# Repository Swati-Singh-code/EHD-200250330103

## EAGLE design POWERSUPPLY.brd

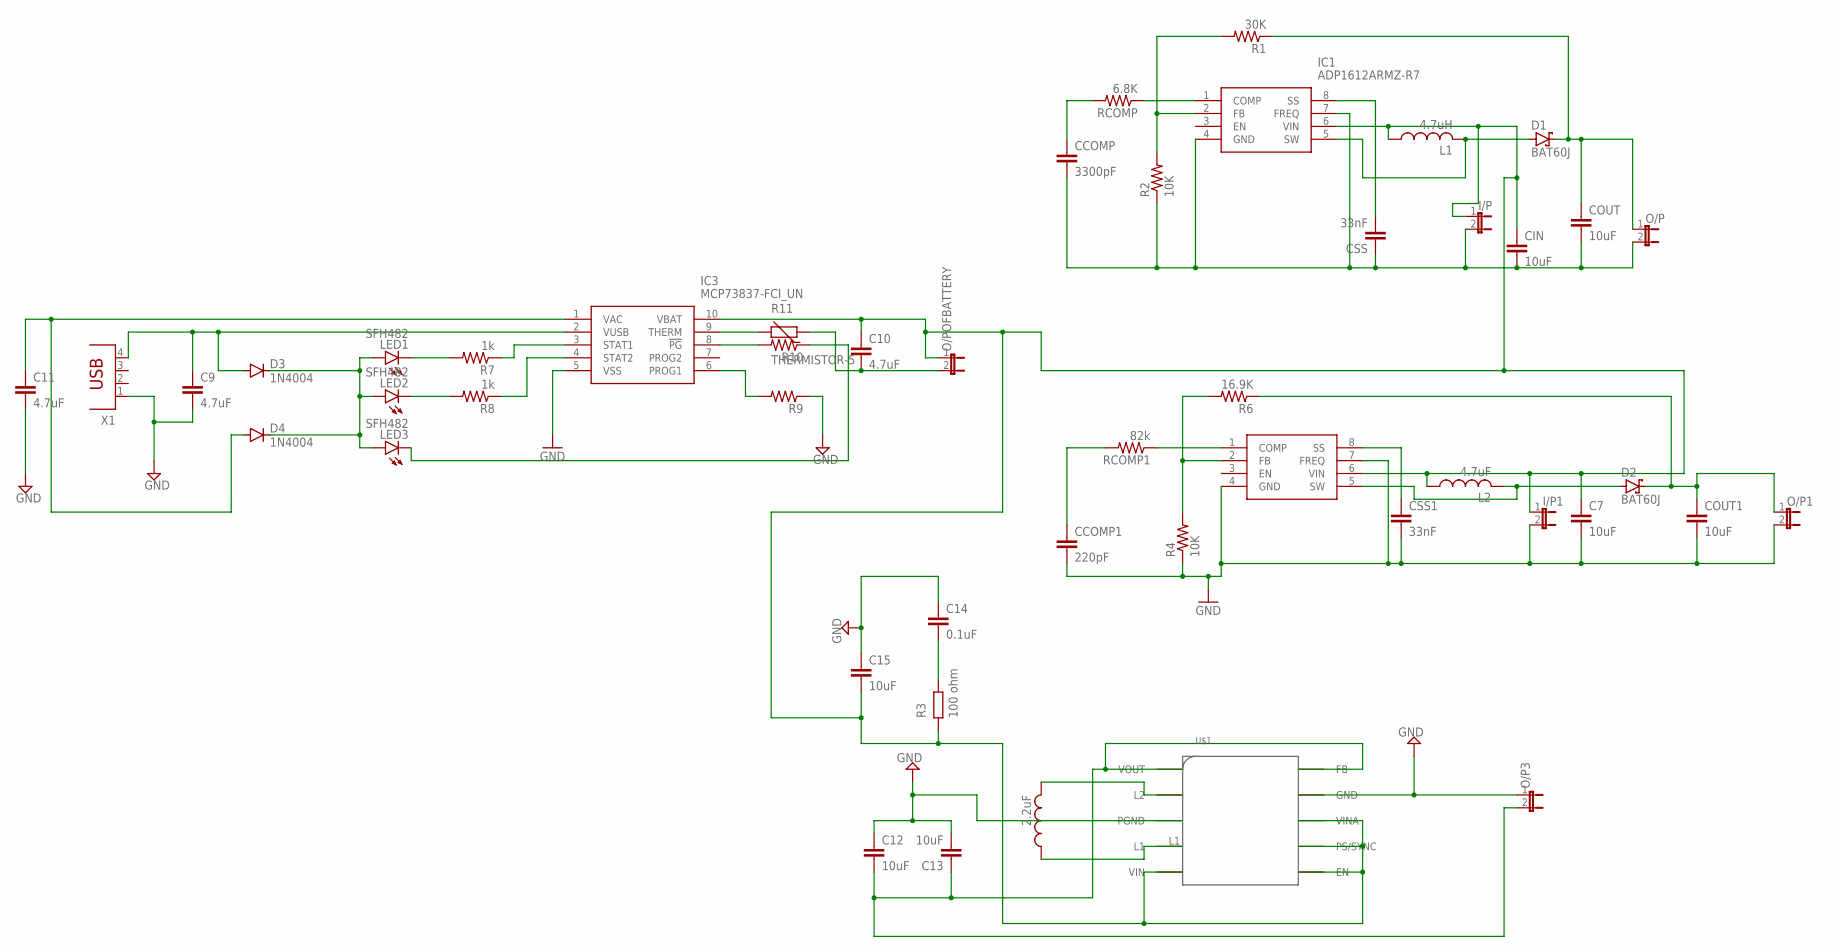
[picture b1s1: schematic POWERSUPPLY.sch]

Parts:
C7, C12, C13, C15: 10uF; C2.5-3
C9, C10, C11: 4.7uF; C2.5-3
C14: 0.1uF; C2.5-3
CCOMP: 3300pF; C2.5-3
CCOMP1: 220pF; C2.5-3
CIN: 10uF; C2.5-3
COUT, COUT1: 10uF; C2.5-3
CSS, CSS1: 33nF; C2.5-3
D1, D2: BAT60J; SOD323_ST
D3, D4: 1N4004; DO41-10
I/P, I/P1: JP1E; JP1
IC1: ADP1612ARMZ-R7; SOP65P490X110-8N
IC2: ADP1613ARMZ-R7; SOP65P490X110-8N
IC3: MCP73837-FCI_UN; SOP50P490X110-10N
L1: 4.7uH; 0207/5V
L2: 4.7uF; 0207/5V
L3: 2.2uF; 0207/5V
LED1, LED2, LED3: SFH482
O/P, O/P3: JP1E; JP1
O/P1: 3.3V; JP1
O/POFBATTERY: JP1E; JP1
R1: 30K; 0204/7
R2, R4: 10K; 0204/7
R6: 16.9K; 0204/7
R7, R8: 1k; 0204/7
R9, R10: R-US_0204/7; 0204/7
R11: THERMISTOR-5; R-5
RCOMP: 6.8K; 0204/7
RCOMP1: 82k; 0204/7
U$1: TPS63002
X1: PN87520

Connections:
GND: C7.2, C9.2, C11.2, C12.1, C13.2, C14.1, C15.1, CCOMP1.2, COUT1.2, CSS1.2, I/P1.2, IC2.4 (GND), IC2.7 (FREQ), IC3.5 (VSS), O/P1.2, O/P3.1, R4.1, R9.1, U$1.GND, U$1.PGND, X1.1
unnamed: CCOMP.1, RCOMP.2
unnamed: IC1.1 (COMP), RCOMP.1
unnamed: CCOMP.2, CIN.2, COUT.2, CSS.1, I/P.2, IC1.4 (GND), IC1.7 (FREQ), O/P.2, R2.1
unnamed: IC1.2 (FB), R1.2, R2.2
unnamed: CSS.2, IC1.8 (SS)
unnamed: IC3.4 (STAT2), R8.1
unnamed: C7.1, C10.1, C15.2, CIN.1, I/P.1, I/P1.1, IC1.6 (VIN), IC2.6 (VIN), IC3.10 (VBAT), L1.1, L2.1, O/POFBATTERY.1, U$1.EN, U$1.PS/SYNC, U$1.VIN, U$1.VINA
unnamed: D1.A, IC1.5 (SW), L1.2
unnamed: COUT.1, D1.C, O/P.1, R1.1
unnamed: CCOMP1.1, RCOMP1.2
unnamed: IC2.1 (COMP), RCOMP1.1
unnamed: IC2.2 (FB), R4.2, R6.2
unnamed: CSS1.1, IC2.8 (SS)
unnamed: D2.A, IC2.5 (SW), L2.2
unnamed: C11.1, D4.A, IC3.1 (VAC)
unnamed: L3.2, U$1.L2
unnamed: COUT1.1, D2.C, O/P1.1, R6.1
unnamed: C9.1, D3.A, IC3.2 (VUSB), X1.4
unnamed: C12.2, C13.1, O/P3.2, U$1.FB, U$1.VOUT
unnamed: IC3.3 (STAT1), R7.1
unnamed: D3.C, D4.C, LED1.A, LED2.A, LED3.A
unnamed: LED1.K (C), R7.2
unnamed: LED2.K (C), R8.2
unnamed: LED3.K (C), R10.1
unnamed: IC3.6 (PROG1), R9.2
unnamed: L3.1, U$1.L1
unnamed: IC3.9 (THERM), R11.2
unnamed: IC3.8 (!PG), R10.2
unnamed: C10.2, O/POFBATTERY.2, R11.1

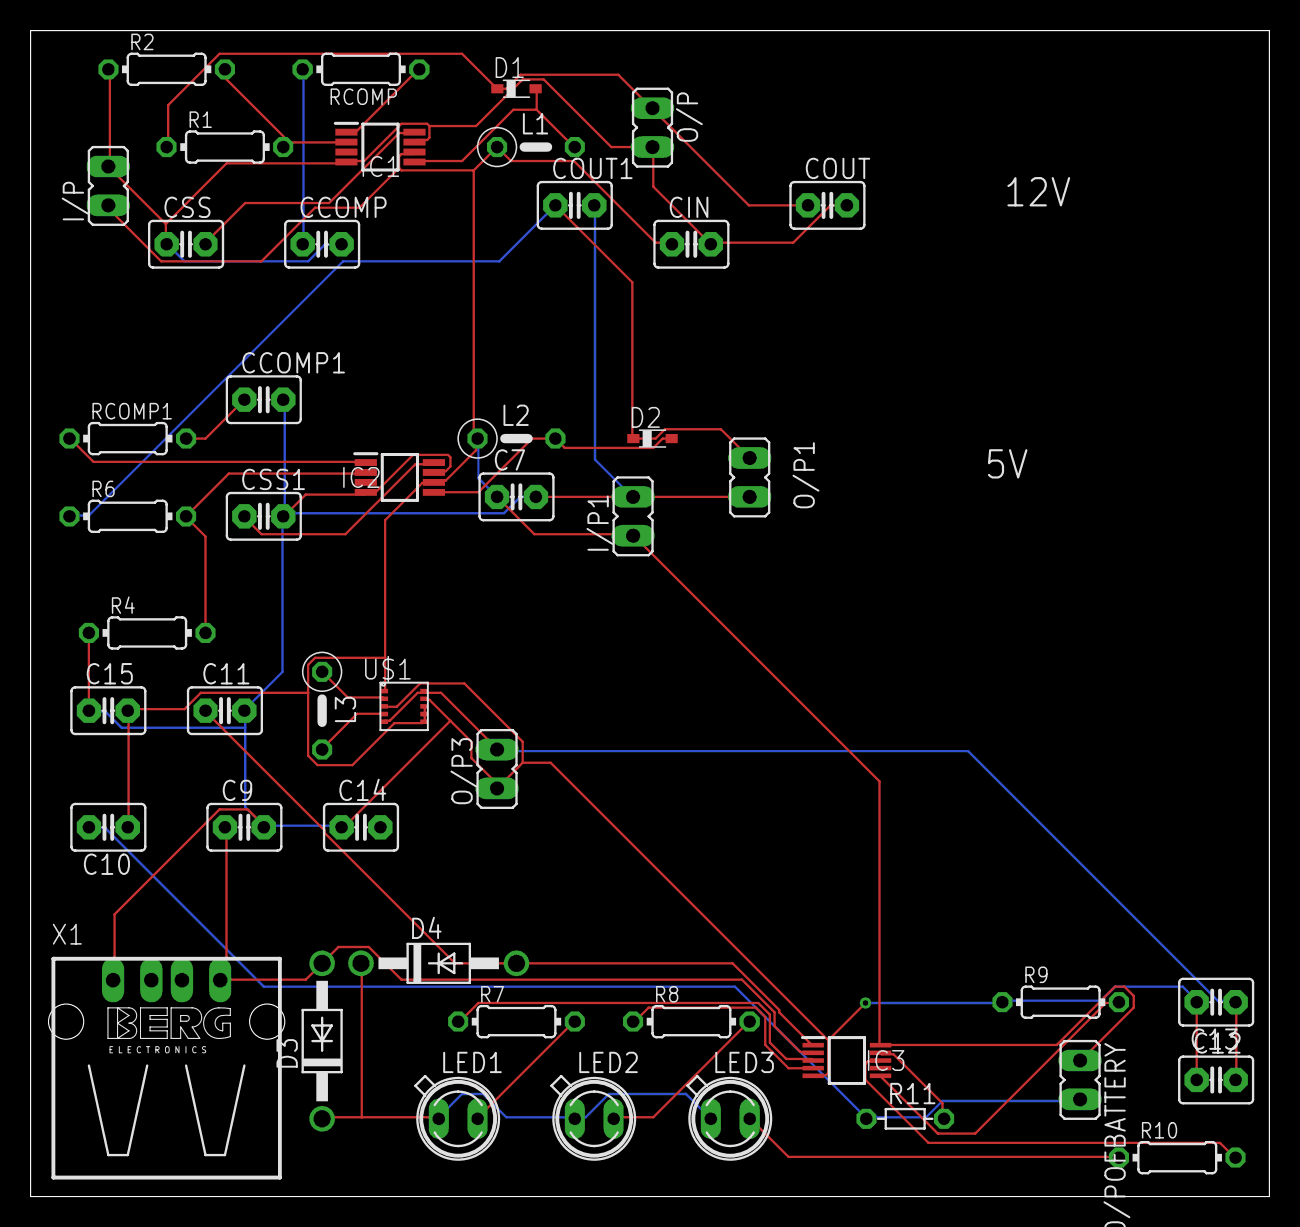
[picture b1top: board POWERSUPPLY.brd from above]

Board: 2 copper layers, 81.0 x 76.2 mm, 47 parts (0 on the bottom side), 30 nets.

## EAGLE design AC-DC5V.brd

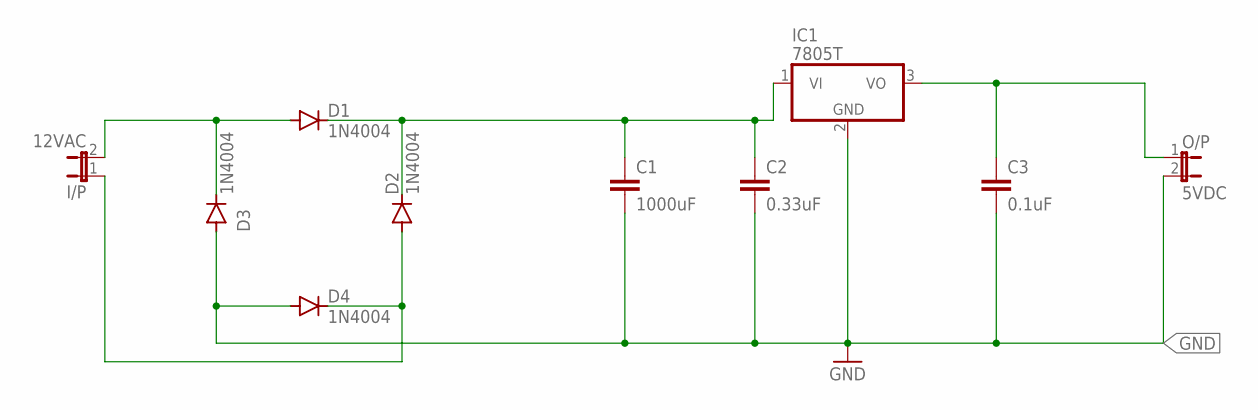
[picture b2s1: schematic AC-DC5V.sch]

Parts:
C1: 1000uF; C2.5-3
C2: 0.33uF; C2.5-3
C3: 0.1uF; C2.5-3
D1, D2, D3, D4: 1N4004; DO41-10
I/P: 12VAC; JP1
IC1: 7805T; TO220H
O/P: 5VDC; JP1

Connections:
GND: C1.2, C2.2, C3.2, D3.A, D4.A, IC1.2 (GND), O/P.2
unnamed: C3.1, IC1.3 (VO), O/P.1
unnamed: C1.1, C2.1, D1.C, D2.C, IC1.1 (VI)
unnamed: D2.A, D4.C, I/P.1
unnamed: D1.A, D3.C, I/P.2

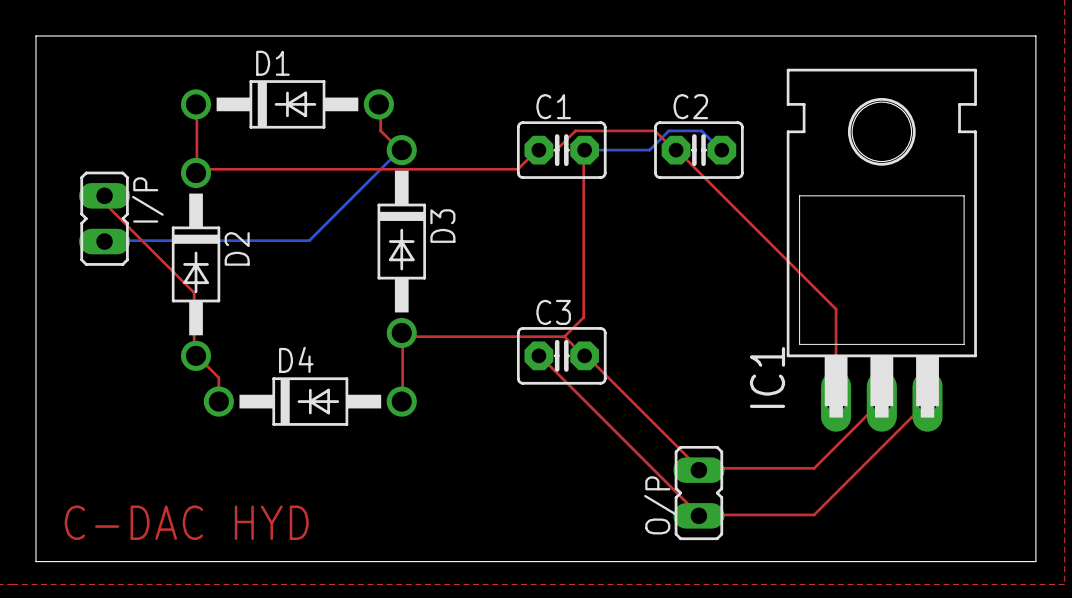
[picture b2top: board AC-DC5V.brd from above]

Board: 2 copper layers, 55.5 x 29.2 mm, 10 parts (0 on the bottom side), 5 nets.

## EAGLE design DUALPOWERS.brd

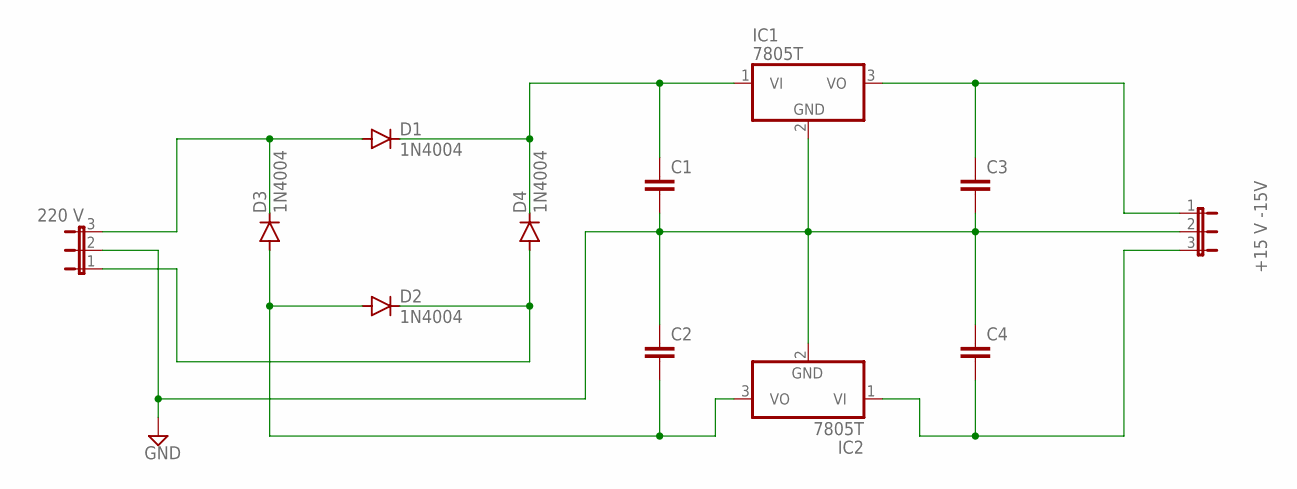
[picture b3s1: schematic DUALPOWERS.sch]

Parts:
-5V_GND_+5V: +15 V -15V; JP2
C1, C2, C3, C4: C2,5-3; C2.5-3
D1, D2, D3, D4: 1N4004; DO41-10
IC1, IC2: 7805T; TO220H
JMP: 220 V; JP2

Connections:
GND: -5V_GND_+5V.2, C1.2, C2.1, C3.2, C4.1, IC1.2 (GND), IC2.2 (GND), JMP.2
unnamed: D1.A, D3.C, JMP.3
unnamed: -5V_GND_+5V.3, C4.2, IC2.1 (VI)
unnamed: C2.2, D2.A, D3.A, IC2.3 (VO)
unnamed: C1.1, D1.C, D4.C, IC1.1 (VI)
unnamed: -5V_GND_+5V.1, C3.1, IC1.3 (VO)
unnamed: D2.C, D4.A, JMP.1

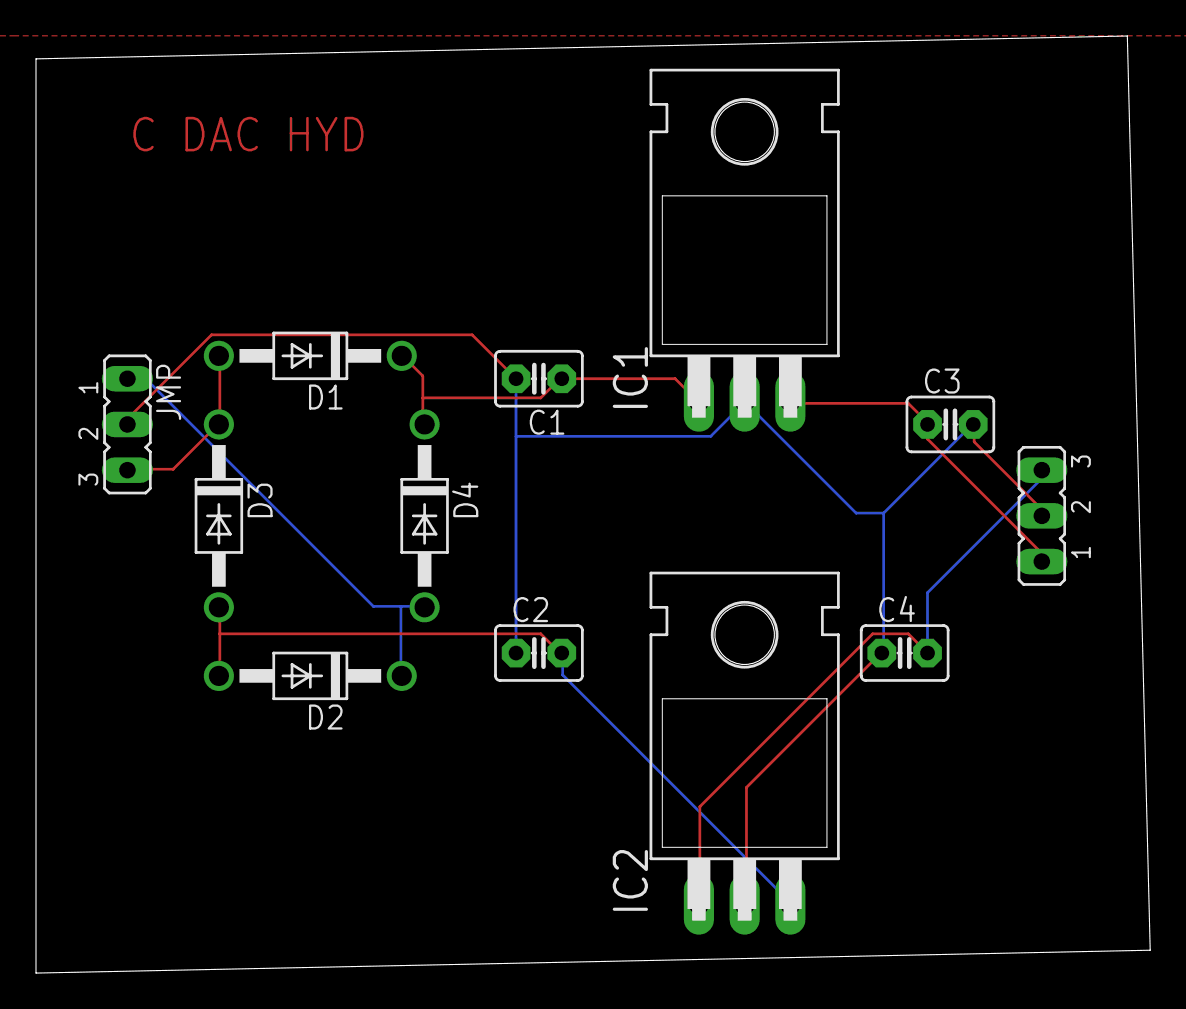
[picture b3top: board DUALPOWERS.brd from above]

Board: 2 copper layers, 61.9 x 52.1 mm, 12 parts (0 on the bottom side), 7 nets.
